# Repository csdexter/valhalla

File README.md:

# Valhalla

This repository contains version-controlled material related to operation
Valhalla. The documentation counterparts are currently stored in Google Drive.

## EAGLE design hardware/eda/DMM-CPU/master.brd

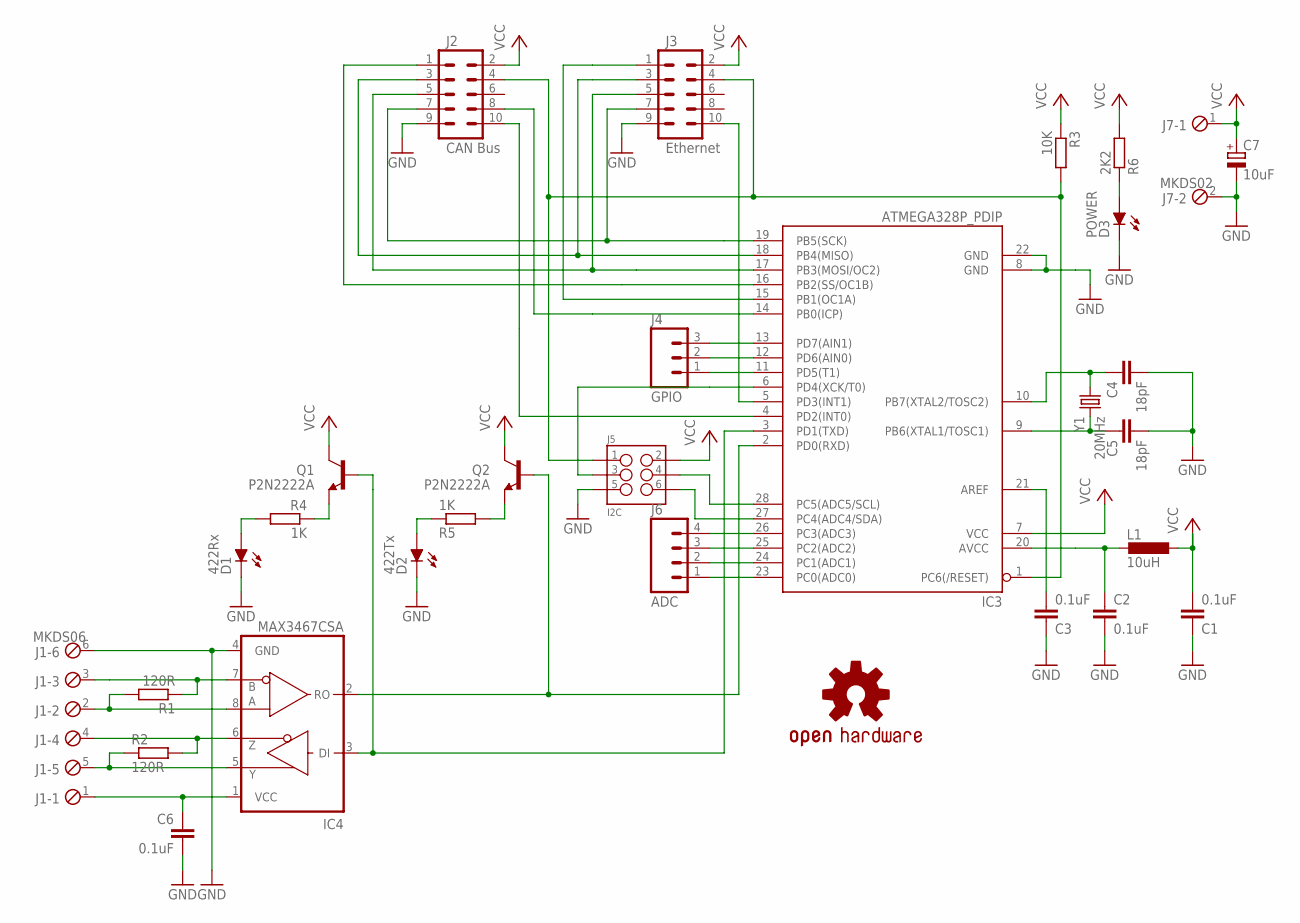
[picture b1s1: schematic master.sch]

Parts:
C1, C2, C3, C6: 0.1uF; C050-025X075
C4, C5: 18pF; C050-024X044
C7: 10uF; E2,5-6
D1: 422Rx; LED3MM
D2: 422Tx; LED3MM
D3: POWER; LED3MM
IC3: ATMEGA328P_PDIP; DIL28-3
IC4: MAX3467CSA; DIL08
J1: MKDS06
J2: CAN Bus; 2X5-SHROUDED
J3: Ethernet; 2X5-SHROUDED
J4: GPIO; 1X03
J5: I2C; 2X3-SHROUDED
J6: ADC; 1X04
J7: MKDS02
L1: 10uH; 0207/5V
LOGO1: OSHW-LOGOM; OSHW-LOGO-M
Q1, Q2: P2N2222A; TO92
R1, R2: 120R; 0207/5V
R3: 10K; 0207/5V
R4, R5: 1K; 0207/5V
R6: 2K2; 0207/5V
Y1: 20MHz; HC49/S

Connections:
422RX_N: IC4.7 (B), J1.3, R1.1
422RX_P: IC4.8 (A), J1.2, R1.2
422TX_N: IC4.6 (Z), J1.4, R2.2
422TX_P: IC4.5 (Y), J1.5, R2.1
GND: C1.1, C2.2, C3.1, C4.2, C5.2, C6.2, C7.-, D1.K (C), D2.K (C), D3.K (C), IC3.8 (GND), IC3.22 (GND), IC4.4 (GND), J1.6, J2.9, J3.9, J5.5, J7.2
unnamed: C2.1, IC3.20 (AVCC), L1.2
unnamed: C5.1, IC3.9 (PB6(XTAL1/TOSC1)), Y1.2
unnamed: C3.2, IC3.21 (AREF)
unnamed: C6.1, IC4.1 (VCC), J1.1
unnamed: C4.1, IC3.10 (PB7(XTAL2/TOSC2)), Y1.1
unnamed: IC3.18 (PB4(MISO)), J2.3, J3.3
unnamed: IC3.6 (PD4(XCK/T0)), J5.3
unnamed: IC3.19 (PB5(SCK)), J2.7, J3.7
unnamed: IC3.16 (PB2(SS/OC1B)), J2.1
unnamed: IC3.11 (PD5(T1)), J4.1
unnamed: IC3.4 (PD2(INT0)), J2.10
unnamed: IC3.1 (PC6(/RESET)), J2.4, J3.4, J5.1, R3.2
unnamed: IC3.12 (PD6(AIN0)), J4.2
unnamed: IC3.13 (PD7(AIN1)), J4.3
unnamed: D2.A, R5.1
unnamed: D3.A, R6.1
unnamed: IC3.3 (PD1(TXD)), IC4.3 (DI), Q1.2 (B)
unnamed: IC3.14 (PB0(ICP)), J2.8
unnamed: D1.A, R4.2
unnamed: Q1.1 (E), R4.1
unnamed: Q2.1 (E), R5.2
unnamed: IC3.28 (PC5(ADC5/SCL)), J5.4
unnamed: IC3.27 (PC4(ADC4/SDA)), J5.6
unnamed: IC3.15 (PB1(OC1A)), J3.1
unnamed: IC3.5 (PD3(INT1)), J3.10
unnamed: IC3.17 (PB3(MOSI/OC2)), J2.5, J3.5
unnamed: IC3.2 (PD0(RXD)), IC4.2 (RO), Q2.2 (B)
unnamed: IC3.23 (PC0(ADC0)), J6.1
unnamed: IC3.24 (PC1(ADC1)), J6.2
unnamed: IC3.25 (PC2(ADC2)), J6.3
unnamed: IC3.26 (PC3(ADC3)), J6.4
VCC: C1.2, C7.+, IC3.7 (VCC), J2.2, J3.2, J5.2, J7.1, L1.1, Q1.3 (C), Q2.3 (C), R3.1, R6.2

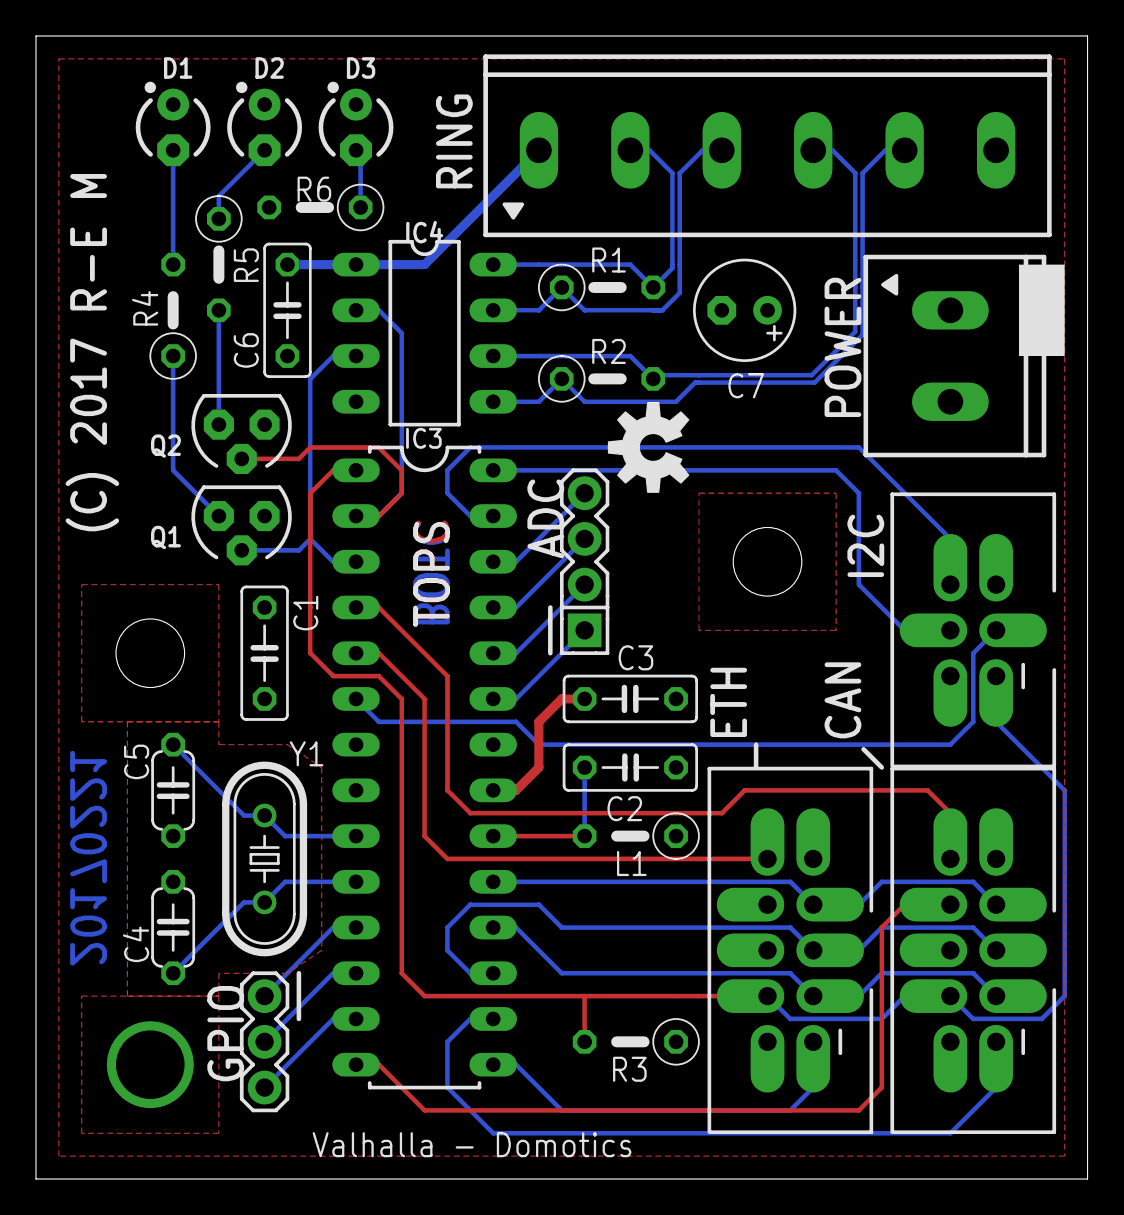
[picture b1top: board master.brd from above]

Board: 2 copper layers, 58.4 x 63.5 mm, 30 parts (0 on the bottom side), 37 nets.

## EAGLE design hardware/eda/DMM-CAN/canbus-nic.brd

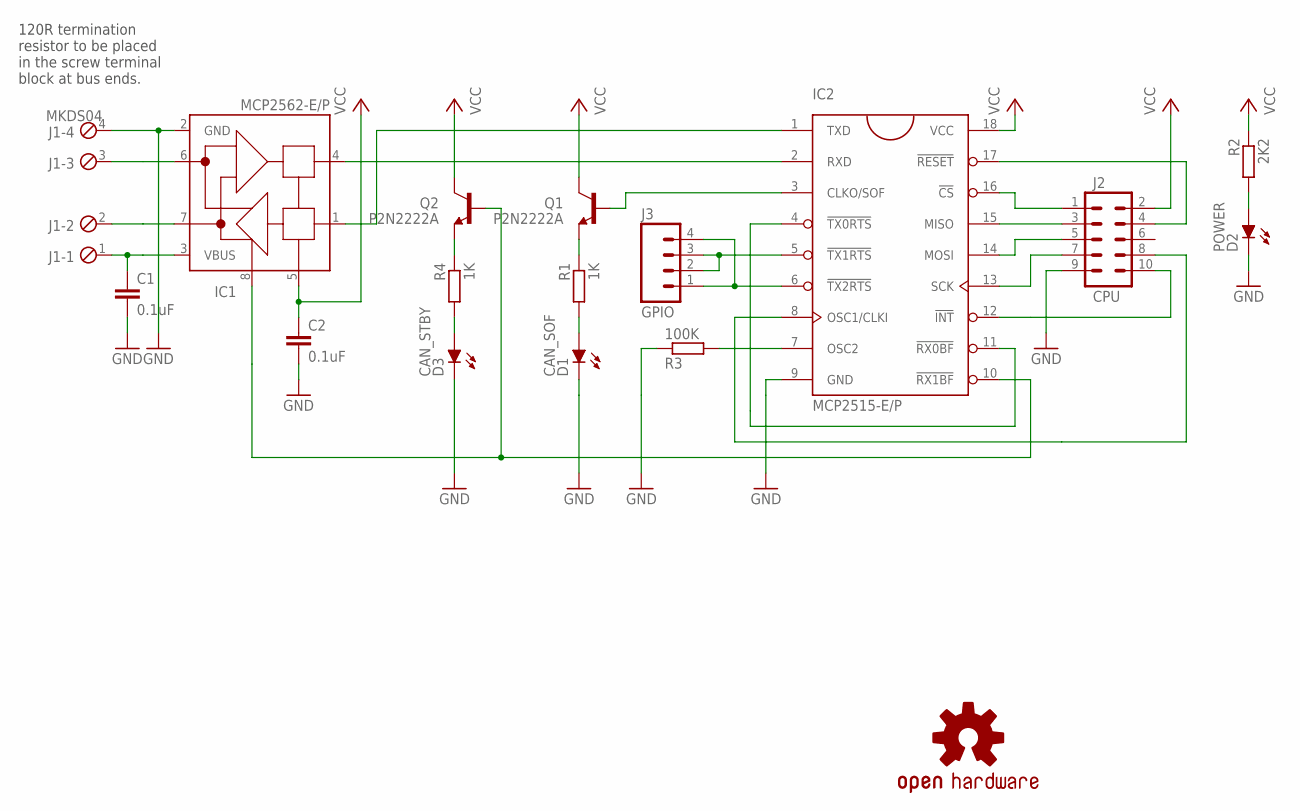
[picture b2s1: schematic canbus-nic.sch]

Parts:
C1, C2: 0.1uF; C050-025X075
D1: CAN_SOF; LED3MM
D2: POWER; LED3MM
D3: CAN_STBY; LED3MM
IC1: MCP2562-E/P; DIL08
IC2: MCP2515-E/P; DIL18
J1: MKDS04
J2: CPU; 2X5-SHROUDED
J3: GPIO; 1X04
LOGO1: OSHW-LOGOMINI; OSHW-LOGO-MINI
Q1, Q2: P2N2222A; TO92
R1, R4: 1K; 0207/5V
R2: 2K2; 0207/5V
R3: 100K; 0207/5V

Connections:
!GPI0: IC2.5 (!TX1RTS), J3.2, J3.3
!GPI1: IC2.6 (!TX2RTS), J3.1, J3.4
GND: C1.2, C2.2, D1.K (C), D2.K (C), D3.K (C), IC1.2 (GND), IC2.9 (GND), J1.4, J2.9, R3.1
unnamed: IC1.1 (TXD), IC2.1 (TXD)
unnamed: IC1.4 (RXD), IC2.2 (RXD)
unnamed: IC1.6 (CANL), J1.3
unnamed: IC1.7 (CANH), J1.2
unnamed: D2.A, R2.2
unnamed: IC1.8 (STBY), IC2.10 (!RX1BF), Q2.2 (B)
unnamed: IC2.15 (MISO), J2.3
unnamed: IC2.7 (OSC2), R3.2
unnamed: IC2.13 (SCK), J2.7
unnamed: IC2.16 (!CS), J2.1
unnamed: D3.A, R4.2
unnamed: IC2.12 (!INT), J2.10
unnamed: IC2.17 (!RESET), J2.4
unnamed: Q2.1 (E), R4.1
unnamed: IC2.8 (OSC1/CLKI), J2.8
unnamed: Q1.1 (E), R1.1
unnamed: D1.A, R1.2
unnamed: IC2.4 (!TX0RTS), IC2.11 (!RX0BF)
unnamed: IC2.3 (CLKO/SOF), Q1.2 (B)
unnamed: C1.1, IC1.3 (VBUS), J1.1
unnamed: IC2.14 (MOSI), J2.5
VCC: C2.1, IC1.5 (VCC), IC2.18 (VCC), J2.2, Q1.3 (C), Q2.3 (C), R2.1

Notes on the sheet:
120R termination resistor to be placed in the screw terminal block at bus ends.

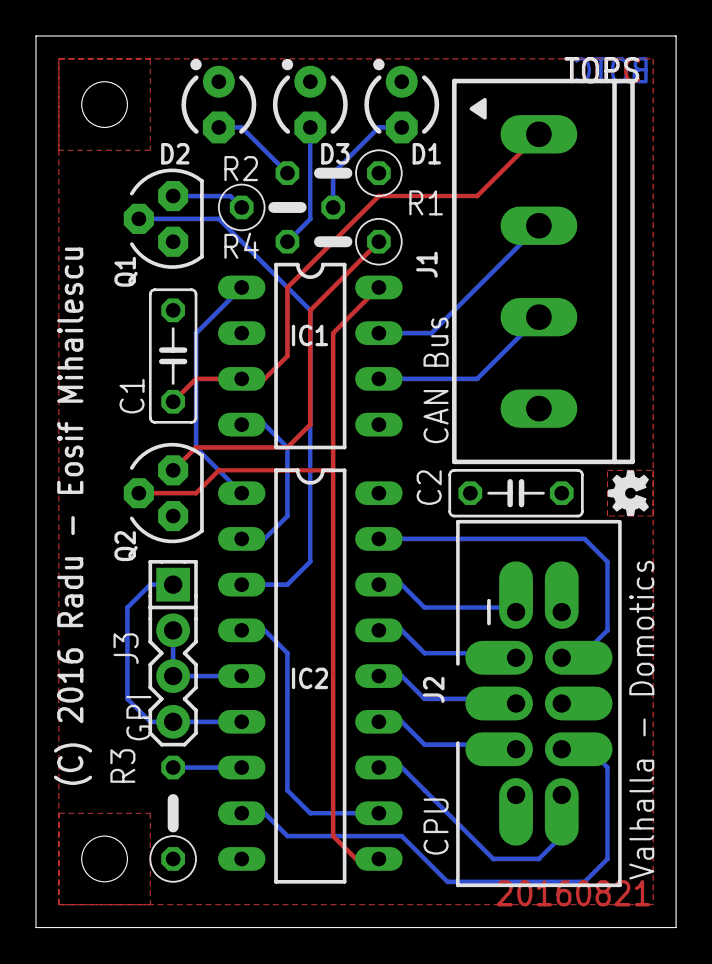
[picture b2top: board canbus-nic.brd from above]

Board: 2 copper layers, 35.6 x 49.5 mm, 17 parts (0 on the bottom side), 25 nets.

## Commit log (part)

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2024-02-06 Initial commit of Valhalla files
2024-02-06 BUGFIX: The Round Tracks plugin ignores design rules - all tracks touched by the plugin will need to be rerouted, this commit marks the beginning of that effort.
2024-02-12 BUGFIX: done cleaning-up after curved track plugin - also switched to 2-pin terminal block for the NTC (there's no use really in exposing the measurement power signal)
2024-02-13 UPDATE: UFH CPU board layout complete
2024-03-17 UPDATES: - initial component selection for cylinder CPU - initial component selection for cylinder Relay Box
2024-03-19 UPDATES: - progress on the Cylinder relay box
2024-04-25 UPDATES: - Cylinder relay box design complete
2024-06-29 BUGFIX: improved page layout for UFH CPU schematic.
2024-06-29 UPDATE: clarified relation between safety interlock loop and heaters.
2024-07-03 UPDATE: last round of changes to UFH and Cylinder relay boxes.
    - this brings the schematics of the two relay boxes to "as built"
    status.
2024-07-05 UPDATE: added cabling plan for hotpress ceiling.
2024-07-06 UPDATE: refined hotpress cabling plan, solved the fan thermostat 2-in-1 issue. - upgraded to KiCAD 8 while at it.
2024-07-06 UPDATE: added CPU cable glands to the hotpress cabling plan.
2024-09-10 UPDATE: minor cosmetic updates to Modbus TCP client & RTU server.
2025-01-03 UPDATE: upgraded to latest KiCAD version and cosmetic adjustments
    - moved Dalas 1-Wire bridge up on UFH Sensor PCB to align with the
    other temperature sensor chips.
2025-01-07 UPDATE: fixed connection of AREF on UFH CPU
    - according to official documentation, ATMega's AREF pin should be
    connected only to a decoupling capacitor. If/when AREF=AVCC is
    desired for an ADC measurement, they can be connected together
    internally via register settings.
2025-01-07 UPDATE: started refactoring into the Valhalla MOD system.
2025-01-07 UPDATE: progress with the CPU(ATMega328) module
    - ATMega328 boilerplate done, BUS and UI done, GPIO done
    - LED UI in progress.
2025-01-12 UPDATE: schematic complete of Valhalla-MOD CPU (ATMega) module
    - we still don't have a solution for powering the LEDs while obeying
    the design constraint that all modules must be agnostic to Vio
    inside [3.3V, 5V]
    - initial PCB component placement hints at 3" height for CPU (ATMega)
    module.
2025-01-18 UPDATE: formal dimensions for Valhalla MOD and progrss on CPU
    - added formal dimensions to the Valhalla MOD PSU PCB, to serve as a
    future template and as documentation
    - changed Zener/Schottky symbols to filled variant on same module,
    as customary in the EU
    - solved the Vio independence issue for the UI LEDs on the CPU module
    with a switchable regulator
2025-01-19 UPDATE: CPU module trace routing complete
    - remaining stuff: crystal dress-up and silkscreen finish-up
    - we may choose not to get artsy on this one (teardrops and curves) due
    to DRC/real estate constraints.
2025-01-24 UPDATE: progress towards templatizing dimensions - used the PSU module as a master copy for now until the template stabilizes, to be exported as a stand-alone blueprint for future modules - minor pro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
2025-01-26 UPDATE: PSU and CPU(ATMega-T) artwork complete
    - also extracted the existing PSU as a template for future modules
    - PSU final touches and RTM
    - CPU(ATMega-T) tied unused inputs to GND, fixed all DRC violations,
    dressed-up silkscreen and RTM.
2025-02-02 ADD: Valhalla-MOD KiCAD template
    - completed packaging of template schematic/board to use as KiCAD
    template
    - authored ICP(AVR-ICSP) using said template as PoC.
2025-02-02 ADD: Valhalla-MOD XVR(RS485)
    - started work on the UART to RS-485 transceiver module, got stuck on
    finding a part that can either work on both 5 and 3.3V OR that has
    5V-tolerant inputs.
2025-02-04 UPDATE: finalized schematic of XVR(RS485)
    - found a solution for Vio transparency using a buck-boost regulator
    module, this in turn opened the way to cheap 5V-powered RS485
    transceivers.
    - done initial component placement on the PCB, routing to follow.
2025-02-07 UPDATE: core transceiver part done for XVR(RS232)
    - drawn and connected core components, placed on PCB tentatively
    - will probably go for the integrated 8P8C+LEDs jack to remain
    compliant with the Valhalla-MOD mechanical standard
    - some assembly time configurability avenues identified, next to
    implement.
2025-02-09 UPDATE: Schematic done for XVR(RS-232)
    - gave up on native modularity in KiCAD, the data model is simply
    broken
    - routing of XVR(RS-232) to commence next.
2025-02-16 UPDATE: XVR(RS-232) done, RTM
    - layout and routing done for XVR(RS-232), including documentation
    for assembly variants and volumetric interference checks.
2025-02-25 UPDATE: started work on XVR(OT+)
    - master/slave interface transceiver schematic done
    - verification of analog parameters of involved parts is pending
2025-03-16 UPDATE: re-touched PSU after latest specification release
    - added LVCC and BVCC and polyfuses on all outputs
    - added simple LVCC control via GPIO
    - layout update to follow.
2025-03-22 UPDATE: MOD-PSU re-layout complete, RTM.
2025-03-25 UPDATE: updated the MOD template to match the latest specification.
2025-03-25 UPDATE: updated MOD-CPU(ATMega) to match the latest specification.
2025-03-25 UPDATE: cosmetic fixes to schematic defaults
2025-03-25 UPDATE: updated MOD-XVR(RS232) to match the latest specification.
2025-03-25 UPDATE: updated MOD-XVR(RS485) to the latest specification.
2025-03-25 CLEANUP: removed hierarchical sub-sheets for UI LEDs
    - the KiCAD data model is, sadly, still not suitable for real
    modularity in real-life projects.
2025-03-30 UPDATE: progress on MOD-XVR(GPIO-OT-T)
    - added UI LEDs
    - added boost converter socket for 24DC
    - added buffering of boiler-side Tx line
    - still need to add opto-isolation for thermostat side.
2025-04-08 UPDATE: minor progress on layout of MOD-XVR(GPIO-OT-I)
    - bulk-grouped by functional blocks, it might all fit afterall.
2025-04-09 UPDATE: further progress with layout of MOD-XVR(OT+)
    - thermostat section done as a group
    - boiler section to follow
    - connections to the rest of the circuit go last.
2025-04-10 UPDATE: MOD-XVR(OT+) net layout complete!
    - it finally all fit in, with some small room to spare
    - silkscreen is next.
2025-04-11 UPDATE: MOD-XVR(OT+) layout complete, RTM!
2025-04-13 ADD: created MOD-BPL(SEP), a bus separator/injector module.
    - schematic done
    - layout done, RTM.
2025-09-13 BUGFIX: thermostat input needs to be OPEN for OpenTherm
    - this fixes a schematic bug in the Cylinder Computer relay box that
    had the boiler's thermostat input automatically shorted upon
    energizing the Computer Control relay
    - this goes against the modus operandi of OpenTherm where the binary
    thermostat input remains open and heat demands are made via
    OpenTherm only.
2025-12-12 UPDATE: 1st routing pass done on MOD-XVR(4IO)
    - netclass will have to be re-checked on GPI-Mains
    - clearance/creepage values between the two GPI lines
    - netclass will have to be re-checked on GPO-Power
    - ampacity of entire high-power loop
    - polarization for the field interface modules to be added
    - GPIO line modules are already polarized
2025-12-14 UPDATE: fixes for MOD-XVR(4IO)
    - fixed clearance/creepage issues on mains GPI FIM
    - fixed 1/2 of loop ampacity issues on power GPO FIM
2025-12-19 UPDATE: silkscreen done on mainboard of XVR(4IO)
    - GPIO FIM mechanical polarization also done
2025-12-21 UPDATE: progess on MOD-XVR(4IO)
    - fixed the other 1/2 of loop ampacity issues on power GPO FIM
    - revised clearance/creepage solution for GPI FIM
    - silkscreen references pass complete for all three FIMs
2025-12-23 UPDATE: finished silkscreen on MOD-XVR(4IO)
    - finalized mechanical details of Timing Module interface to
    Watchdog/Debouncer module
    - finalized silkscreen of all daughtercards
    - overhanging parts on main board still need their silkscreen clipped
    to the board edge.
2025-12-26 UPDATE: MOD-XVR(4IO) done, RTM (panelizing required)
    - fixed silkscreen overhanging the board edge on mainboard
    - ran DRC and fixed or approved all issues
    - we're done here, RTM
    - splitting by sub-pcb and generating Gerbers separately will be done
    on order day (especially since needed sub-pcb quantity differs from
    one).
2026-01-02 UPDATE: improved LVCC rail usage on MOD-XVR(4IO)
    - LVCC now powers the LEDs, the buffer driving them is powered by
    DVCC, this avoids transients caused by UI changes to propagage
    on the digital power rail
    - 74HC04 was replaced by 74HC125
    - also added decoupling capacitors to all logic chips that required
    them
2026-01-02 UPDATE: progress on MOD-PSU
    - refined the schematic design and started work on the PCB layout
    - selected some critical components, resolved final footprints
    for others
    - found a good compromise for the (initially) /RESET line: using a
    supervisory circuit BUT using it as a POWER_GOOD output. A
    connected CPU can thus choose whether to interpret that as PG
2026-01-07 UPDATE: MOD-PSU revamped schematic should be done
    - allowed for all assembly variants:
    - single AC supply
    - single DC supply
    - dual AC/DC supply with ideal diode OR-ing
    - allowed for remote on/off option for both types of supplies
    - layout is next.
2026-01-11 UPDATE: tentative component placement for MOD-PSU
    - everything fits with room to spare
    - clearance/creepage for the mains section appears fine
    - zones/slots are next.
2026-01-12 UPDATE: progress on MOD-PSU layout
    - zones and slots done
    - heatsink pours and stiches done
    - routing is next.
2026-01-14 UPDATE: progress on MOD-PSU
    - routing done, including copper heatsinks
    - silkscreen is last.
2026-01-18 DONE: MOD-PSU silkscreen complete, DRC pass, RTM
    - also backfilled constraints files for both MOD-PSU and MOD-XVR(4IO)
    - mechanical extraction and specification update is next, then update
    of the template, then on to MOD-CPU(ATMega).
2026-01-25 ADD: Started work on the Valhalla-MOD MCAD
    - owing to the overall context, this will be in FreeCAD (i.e. real
    files on real media)
    - initial version added, created some parts, still have to optimize
    the parametric data model, but it's coming along nicely
    - final (composite) parts follow and assembly will be last.
2026-01-27 UPDATE: progress on the card cage
    - added the PCB support rail which will double as a vertical pillar
    for the corners
    - refined the right angle so that an M3 nut actually fits inside
    - tentatively added PCB support rail holes on front bar, they may need
    to move if the on-top/on-bottom split is changed later.
2026-04-06 Synched the Colored Thread Pool project over for safekeeping
    - updated Bazel configuration to contemporary standards
    (WORKSPACE -> MODULE)
    - initial commit of the Colored Thread Pool project, the configuration
    object and unit tests
    - work in progress, still got a few rough edges and more test coverage
    needed before we can move to the thread pool per se.
2026-04-11 Another sync for the Colored Thread Pool
    - the configuration object and accompanying unit tests are done
    - work moves over to the thread pool proper.
2026-04-11 UPDATE: - progress on the tread pool proper: - cleaned up 1st iteration code - defined per pool structures - skeleton outer worker complete - next steps: - quota work on execution (concurrency) - sub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

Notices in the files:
hardware/eda/DMM-CAN/canbus-nic.brd:
(C) 2016 Radu - Eosif Mihailescu
hardware/eda/DMM-CPU/master.brd:
(C) 2017 R-E M
parts and their libraries:
SparkFun-Connectors-mine: Licensing: Creative Commons ShareAlike 4.0 International - https://creativecommons.org/licenses/by-sa/4.0
SparkFun-DigitalIC-mine: Licensing: CC v3.0 Share-Alike You are welcome to use this library for commercial purposes.
